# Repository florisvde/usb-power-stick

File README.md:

# USB Power Stick
The USB Power Stick is a USB Stick to control power (up to 1 A) to a USB powered device from a PC or SBC.

## Motivation
The Stick is inspired by the common [USB relay sticks](https://aliexpress.com/item/4001216792789.html). 
But using that stick to switch USB power on and off is messy: it requires cutting a USB extention cord, connecting the relay in between and takes up two USB ports. Leading to contraptions like this:

The USB Power Stick solves that problem neatly by providing the switched power on a USB Type A socket. 

The Stick is used to turn an [IKEA HÅRTE](https://www.ikea.com/nl/nl/p/harte-led-bureaulamp-zwart-zilverkleur-20527242/) light on and off using a Python script running on a Raspberry Pi. The light is used to illuminate a 3D printer, controlled by Octoprint, so a webcam can track the printer's progression during the night.

## How does it work
Take a look at the [PDF of the schematic](https://github.com/florisvde/usb-power-stick/blob/main/KiCad/usb-power-stick/usb-power-stick-schematic.pdf). 
The Stick makes use of a USB to serial converter, a flip flop and an output transistor to switch power on and off to the device connected to the Stick's output. The Stick does not provide USB connectivity to the Stick's output.

The RTS line of the serial converter can be controlled from a computer while the port is open. Therefore the RTS line is connected to the flip flop's (FF) data input (D) and the TX line to the FF's clock input (C). By sending a character the FF latches the current RTS state to the FF's output (Q), then the port can be closed again. This allows for a script to periodically turn power to the device on or off when needed.

An RC network is connected to the FF's asynchronous ~R input, to make sure the stick starts up in the off state, a so called Power on Reset (PoR) circuit.

## Build your own
You can send the Gerber files (directly downloadable as zip from the [releases page](https://github.com/florisvde/usb-power-stick/releases)) to any PCB manufacturer and have the boards made. The board is designed with manual assembly in mind, all parts are easily soldered using a standard soldering iron, fine solder and a pair of tweezers. For everything but the passives a shop link is provided in the [Bill of Materials (BOM)](https://github.com/florisvde/usb-power-stick/blob/main/KiCad/usb-power-stick/usb-power-stick-bom.md).
Pay attention to the pin 1 marker (triangle) of D1: the silk screened triangle is correct, the silk screened outline of the part is not!

## Use it
1. Install [Python](https://www.python.org/downloads/) for your OS.
1. Install the [PySerial package](https://pypi.org/project/pyserial/).
1. Plug the Stick into an computer.
1. Find the Stick's *device dev path* (Unix) by running `ls /dev/ttyUSB*` or *COM port* (Windows) by going to Device Manager.
1. Clone or download this repository.
1. Edit the `stick_on.py` and `stick_off.py` files to use the correct device dev path or COM port.
1. In the directory containing the scripts, run `python stick_on.py` to turn power to the load on, and run `python stick_off.py` to turn power to the load off.

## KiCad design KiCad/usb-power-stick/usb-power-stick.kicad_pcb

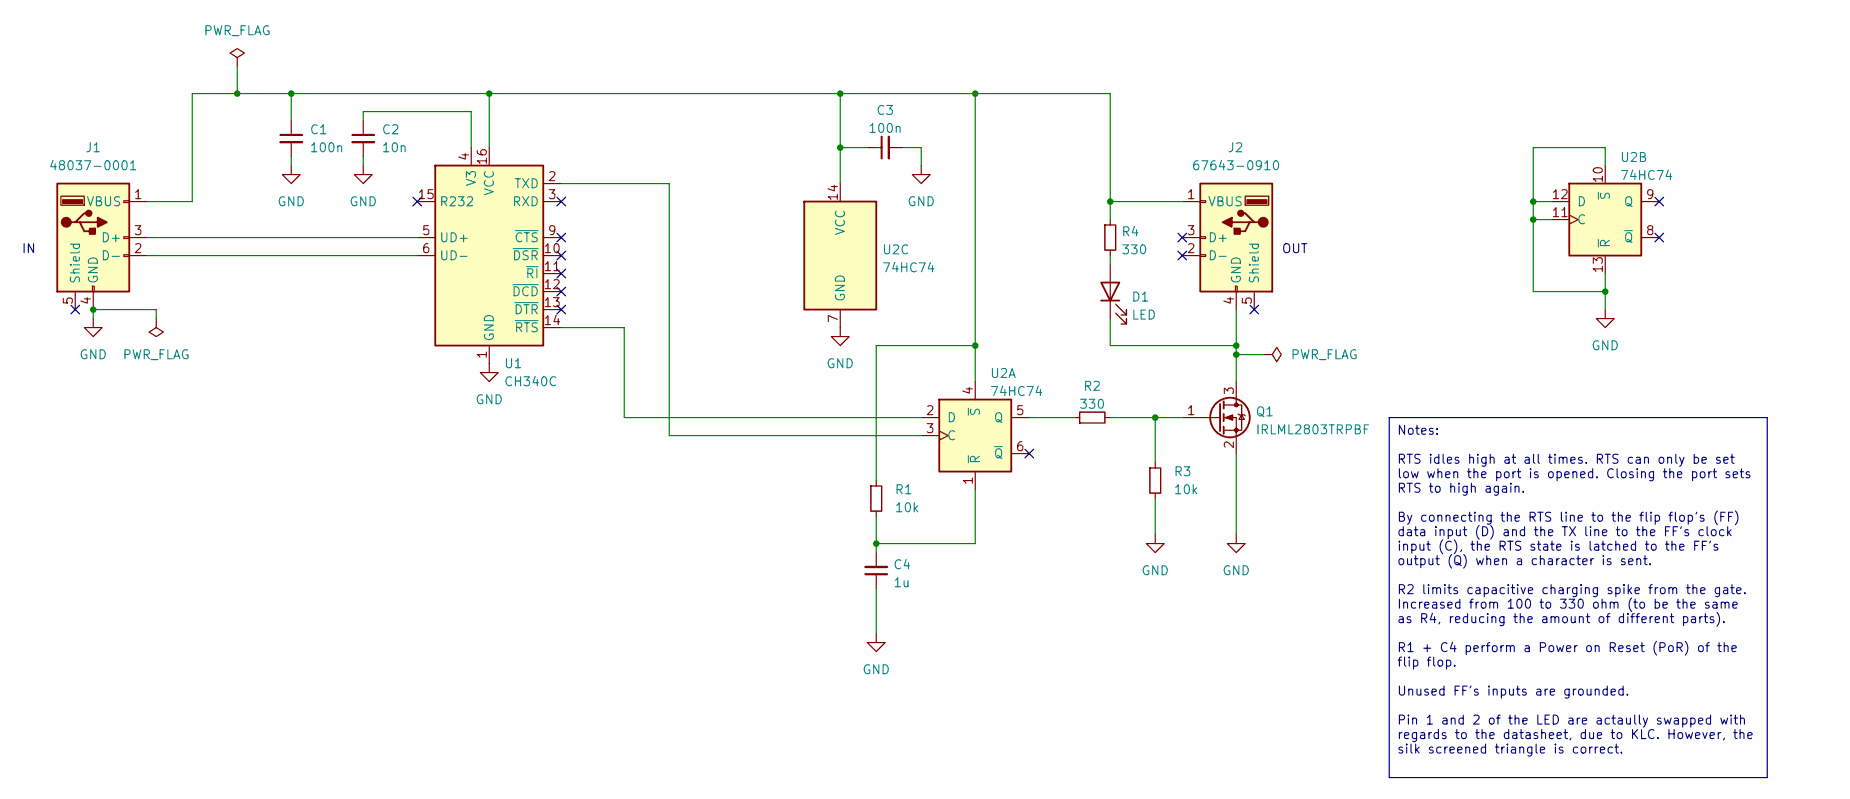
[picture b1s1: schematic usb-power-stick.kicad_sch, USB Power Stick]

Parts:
C1, C3: 100n; R_0805_2012Metric
C2: 10n; R_0805_2012Metric
C4: 1u; R_0805_2012Metric
D1: LED; LED_0805_2012Metric; Farnell 1318244
J1: 48037-0001; Molex_48037-0001; Farnell 2067044
J2: 67643-0910; USB_A_Molex_67643_Horizontal; Farnell 1450206
Q1: IRLML2803TRPBF; SOT-23; Farnell 9102701
R1, R3: 10k; R_0805_2012Metric
R2, R4: 330; R_0805_2012Metric
U1: CH340C; SOIC-16_3.9x9.9mm_P1.27mm
U2: 74HC74; SOIC-14_3.9x8.7mm_P1.27mm; Farnell 1201317

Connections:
GND: C1.2, C2.2, C3.2, C4.1, J1.4 (GND), Q1.2 (S), R3.2, U1.1 (GND), U2.7 (GND), U2.10 (~S), U2.11 (C), U2.12 (D), U2.13 (~R)
unnamed: C1.1, C3.1, J1.1 (VBUS), J2.1 (VBUS), R1.1, R4.1, U1.16 (VCC), U2.4 (~S), U2.14 (VCC)
unnamed: C2.1, U1.4 (V3)
unnamed: J1.2 (D-), U1.6 (UD-)
unnamed: J1.3 (D+), U1.5 (UD+)
unnamed: D1.1 (K), J2.4 (GND), Q1.3 (D)
unnamed: Q1.1 (G), R2.2, R3.1
unnamed: R2.1, U2.5 (Q)
unnamed: D1.2 (A), R4.2
unnamed: U1.2 (TXD), U2.3 (C)
unnamed: U1.14 (~RTS), U2.2 (D)
unnamed: C4.2, R1.2, U2.1 (~R)

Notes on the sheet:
Notes: RTS idles high at all times. RTS can only be set low when the port is opened. Closing the port sets RTS to high again. By connecting the RTS line to the flip flop's (FF) data input (D) and the TX line to the FF's clock input (C), the RTS state is latched to the FF's output (Q) when a charact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
OUT

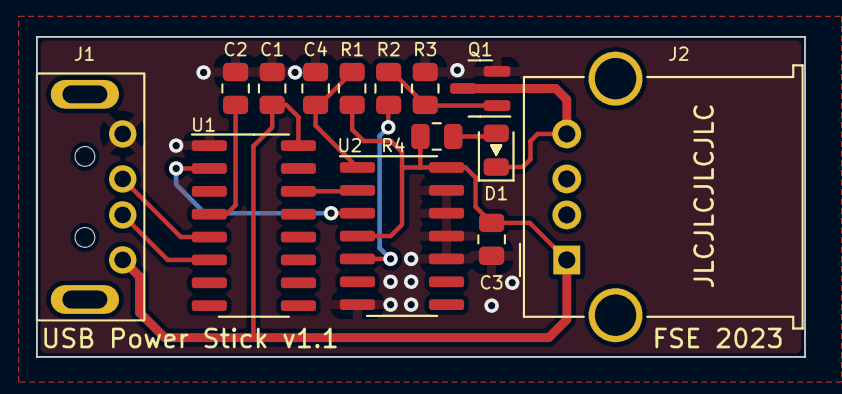
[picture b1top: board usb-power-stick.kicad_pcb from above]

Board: 2 copper layers, 42.7 x 17.8 mm, 14 parts (0 on the bottom side), 12 nets.

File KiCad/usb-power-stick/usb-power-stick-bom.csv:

"Reference","Value","Footprint","Datasheet","Farnell","link","Qty"
"C1, C3","100n","Resistor_SMD:R_0805_2012Metric","~","~","~","2"
"C2","10n","Resistor_SMD:R_0805_2012Metric","~","~","~","1"
"C4","1u","Resistor_SMD:R_0805_2012Metric","~","~","~","1"
"D1","LED","LED_SMD:LED_0805_2012Metric","https://www.farnell.com/datasheets/622356.pdf","1318244","https://nl.farnell.com/1318244","1"
"J1","48037-0001","kicad_custom_parts:Molex_48037-0001","https://www.japanese.molex.com/content/dam/molex/molex-dot-c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","2067044","https://nl.farnell.com/2067044","1"
"J2","67643-0910","Connector_USB:USB_A_Molex_67643_Horizontal"," https://www.japanese.molex.com/content/dam/molex/molex-dot-c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","1450206","https://nl.farnell.com/1450206","1"
"Q1","IRLML2803TRPBF","Package_TO_SOT_SMD:SOT-23","https://www.infineon.com/dgdl/Infineon-IRLML2803-DataSheet-v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","9102701","https://nl.farnell.com/9102701","1"
"R1, R3","10k","Resistor_SMD:R_0805_2012Metric","~","~","~","2"
"R2, R4","330","Resistor_SMD:R_0805_2012Metric","~","~","~","2"
"U1","CH340C","Package_SO:SOIC-16_3.9x9.9mm_P1.27mm","http://www.wch-ic.com/downloads/CH340DS1_PDF.html","","https://www.lcsc.com/product-detail/USB-ICs_WCH-Jiangsu-Qin-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","1"
"U2","74HC74","Package_SO:SOIC-14_3.9x8.7mm_P1.27mm","https://assets.nexperia.com/documents/data-sheet/74HC_HCT74.pdf","1201317","https://nl.farnell.com/1201317","1"

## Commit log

2023-05-25 Create LICENSE
2023-05-26 version 1.1 initial commit
    Added version 1.1 of the PCB, the Python scripts, CHANGES file a photo of the PCB. Updated README.
2023-05-26 updated README and gitignore
    Updated README with more instructions, a motivation and a picture of the old solution. Adjusted gitignore file to include csv files, so the csv BOM file is added.
2023-05-31 fixed stick not turning off on Raspberry Pi
    Closing the port directly after sending the byte did not clock in RTS properly on a Raspberry Pi. Therefore added a delay before closing.
2023-05-31 simplified example scripts
    Simplified the example scripts and removed commented code. Updated deprecated setRTS to rts.

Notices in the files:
KiCad/usb-power-stick/usb-power-stick.kicad_sch:
https://ohwr.org/project/cernohl/wikis/Documents/CERN-OHL-version-2
Released under the CERN Open Hardware Licence Version 2 - Strongly Reciprocal:
